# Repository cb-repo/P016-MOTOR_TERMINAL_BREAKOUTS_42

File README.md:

# 42mm MOTOR TERMINAL BREAKOUT v1.0 (2-pack)

Motor terminals are traditionally small and flimsy, making it hard to guarantee a reliable solder connection.
MOTOR TERMINAL BREAKOUTS are designed to simplify and strengthen these solder joints, enabling more reliable operation especally in high vibration environments: orignially designed for combat robotics but is suitable for any application using these motors. 
  
This is a [New Zealand](https://www.google.co.nz/maps/place/Christchurch+New+Zealand) based product by [cb-technology](https://www.cb-technology.co.nz/), Connor Benton.

## FEATURES
- Mounts to the motor at 0°, 45°, 90°, and 135° angles.
- Large pads with holes to enable stronger connections to the wires.
- Pads are broken out onto PCB fingers allowing the wires to be heatshrunk post soldering (providing even greater mechanical strength).
- 100nF capacitor across the motor output to filter noise and voltage spikes.

## SPECIFICATIONS
- **Dimensions:** 42x53.5x1.6 mm
- **Weight:** 1g each
- **Material:** Fiberglass (FR4)
- **Mounting Pad Center:** 35mm
- **Included in Package:** 2x Motor Terminal Breakouts

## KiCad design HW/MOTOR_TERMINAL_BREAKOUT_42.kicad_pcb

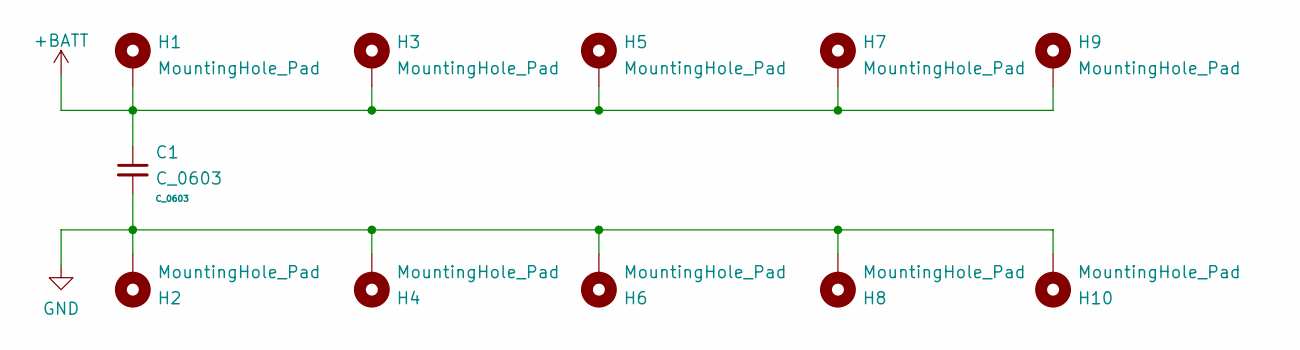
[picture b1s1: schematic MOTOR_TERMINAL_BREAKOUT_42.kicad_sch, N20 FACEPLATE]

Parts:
C1: C_0603
H1, H2: MountingHole_Pad; MountingHole_6mm_Pad_TopBottom
H3, H4, H5, H6, H7, H8, H9, H10: MountingHole_Pad; MountingHole_3mm_Pad_TopBottom

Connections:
+BATT: C1.1, H1.1, H3.1, H5.1, H7.1, H9.1
GND: C1.2, H2.1, H4.1, H6.1, H8.1, H10.1

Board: 4 copper layers, 12 parts (0 on the bottom side), 2 nets, no tracks yet.

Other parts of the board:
H13: MountingHole_Pad; MountingHole_6.5mm

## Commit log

2022-07-19 Initialise LFS in Repo
2022-07-31 Generate First Revision Breakout for 42mm Motor
2022-08-09 Update README for release to CRNZ
